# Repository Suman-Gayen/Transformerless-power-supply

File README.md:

# 🔌 Transformerless Power Supply PCB Design

A compact **Transformerless Power Supply Circuit** designed using **KiCad EDA 9.0.2** that converts AC mains voltage into regulated **5V DC output** without using a transformer.

---

## 📌 Project Overview

This project demonstrates the design of a low-cost transformerless power supply using:

- Capacitive voltage dropping
- Bridge rectification
- Filtering capacitors
- Zener protection
- LM7805 voltage regulation

The circuit is designed for low-power electronic applications where compact size and low component cost are important.

---

## 🖼 Project Schematic

```md

```

---

## ⚙ Features 

- AC to DC conversion
- 5V regulated DC output
- Compact PCB design
- Low component count
- LED power indication
- Overvoltage protection using Zener diode

---

## 🛠 Software Used

| Tool | Version |
|------|---------|
| KiCad EDA | 9.0.2 |

---

## 🔩 Components Used

| Component | Value / Part |
|-----------|--------------|
| U1 | LM7805 Voltage Regulator |
| D1–D4 | 1N4007 Rectifier Diodes |
| D5–D6 | Zener Diodes |
| D7 | LED |
| C1 | 0.1µF Capacitor |
| C2 | 100µF Capacitor |
| C3 | 2.2µF Capacitor |
| C4 | 470µF Capacitor |
| R1 | 1MΩ Resistor |
| R2, R3 | 20KΩ Resistors |
| R4 | 2.2KΩ Resistor |

---

## 🔍 Working Principle

### 1. Capacitive Voltage Dropping
The AC mains voltage is reduced using a non-polarized capacitor instead of a bulky transformer.

### 2. Rectification
Diodes D1–D4 form a bridge rectifier that converts AC voltage into pulsating DC.

### 3. Filtering
Capacitors smooth the rectified DC signal and reduce ripple voltage.

### 4. Voltage Regulation
The LM7805 regulator provides stable 5V DC output.

### 5. Protection
Zener diodes help protect the circuit from voltage spikes and overvoltage conditions.

---

## 📐 PCB Design Highlights

- Designed in KiCad EDA
- Compact component placement
- Easy routing structure
- Beginner-friendly PCB layout
- Suitable for low-power embedded applications

---

## ⚠ Safety Warning

> This project directly interfaces with AC mains voltage.

### Important Safety Notes:
- Do NOT touch the circuit while powered.
- Use proper insulation.
- Test carefully using safety precautions.
- Recommended for educational purposes only.
- Isolation transformer is recommended during testing.

---

## 🎯 Learning Outcomes

Through this project, I learned:

- Transformerless power supply design
- AC to DC rectification
- Voltage regulation using LM7805
- PCB schematic creation in KiCad
- Power electronics fundamentals
- Importance of electrical safety

---

## 🚀 Future Improvements

- Add fuse protection
- Add MOV surge protection
- Improve PCB isolation spacing
- Add output filtering enhancements
- Design compact single-layer PCB

---

## 📂 Project Structure

```bash
Transformerless-Power-Supply/
│
├── Schematic/
├── PCB_Layout/
├── Gerber_Files/
├── Images/
├── BOM/
└── README.md
```

---

## 🧠 Skills Demonstrated

- PCB Design
- Power Electronics
- KiCad EDA
- Circuit Design
- Hardware Development
- Electronic Prototyping

---

## 👨‍💻 Author

**Suman**  
Electronics & PCB Design Enthusiast

---

## 📜 License

This project is open-source and available for learning and educational purposes.

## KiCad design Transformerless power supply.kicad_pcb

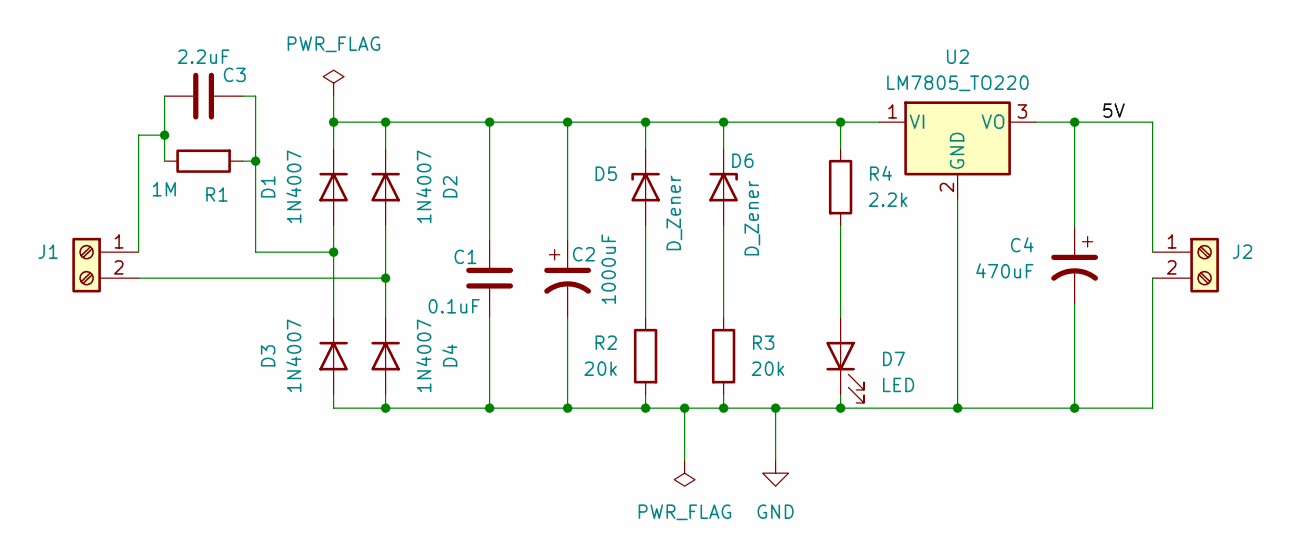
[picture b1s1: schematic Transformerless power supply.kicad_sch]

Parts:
C1: 0.1uF; C_Disc_D3.0mm_W1.6mm_P2.50mm
C2: 1000uF; CP_Radial_D10.0mm_P5.00mm
C3: 2.2uF; C_Rect_L18.0mm_W6.0mm_P15.00mm_FKS3_FKP3
C4: 470uF; CP_Radial_D10.0mm_P3.80mm
D1, D2, D3, D4: 1N4007; D_DO-41_SOD81_P10.16mm_Horizontal
D5, D6: D_Zener; D_A-405_P7.62mm_Horizontal
D7: LED; LED_D5.0mm
J1, J2: Screw_Terminal_01x02; TerminalBlock_bornier-2_P5.08mm
R1: 1M; R_Axial_DIN0207_L6.3mm_D2.5mm_P7.62mm_Horizontal
R2, R3: 20k; R_Axial_DIN0207_L6.3mm_D2.5mm_P7.62mm_Horizontal
R4: 2.2k; R_Axial_DIN0207_L6.3mm_D2.5mm_P7.62mm_Horizontal
U2: LM7805_TO220; TO-220-3_Vertical

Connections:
/5V: C4.1, J2.1, U2.3 (VO)
GND: C1.2, C2.2, C4.2, D3.2 (A), D4.2 (A), D7.1 (K), J2.2, R2.2, R3.2, U2.2 (GND)
unnamed: C3.2, D1.2 (A), D3.1 (K), R1.2
unnamed: C1.1, C2.1, D1.1 (K), D2.1 (K), D5.1 (K), D6.1 (K), R4.1, U2.1 (VI)
unnamed: D2.2 (A), D4.1 (K), J1.2
unnamed: D5.2 (A), R2.1
unnamed: D6.2 (A), R3.1
unnamed: D7.2 (A), R4.2
unnamed: C3.1, J1.1, R1.1

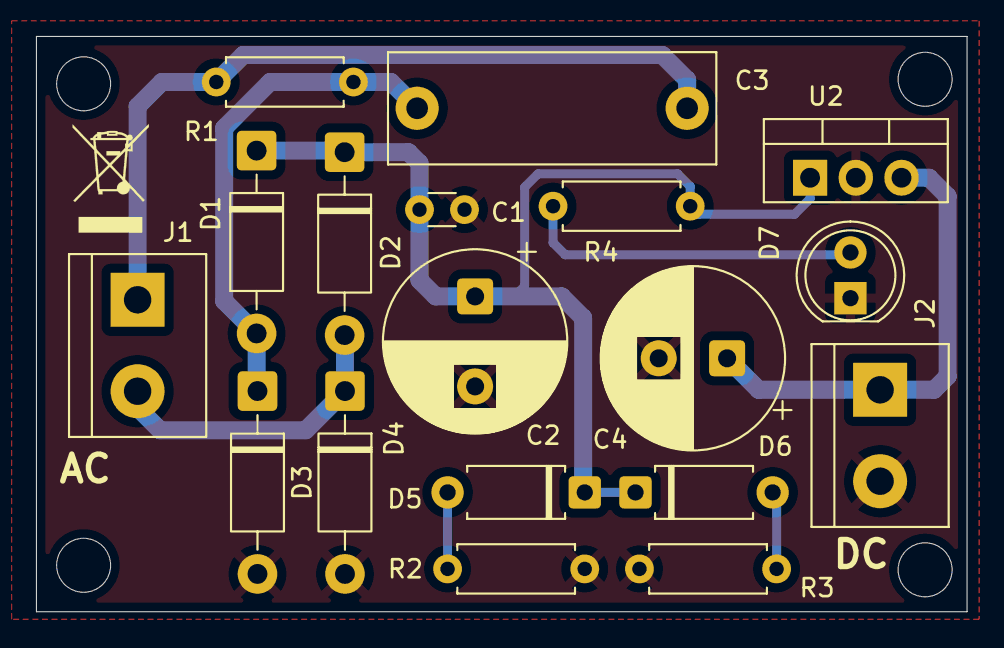
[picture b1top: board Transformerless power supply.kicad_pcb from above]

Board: 2 copper layers, 51.7 x 32.0 mm, 18 parts (0 on the bottom side), 9 nets.

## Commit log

2026-05-17 Revise README for Transformerless Power Supply project
    Updated README to provide detailed project information, including features, components, working principles, safety warnings, and future improvements.
2026-05-17 rename
2026-05-17 Remove placeholder for schematic image in README
    Remove placeholder text for schematic image.
2026-05-17 Fix formatting of Features section in README
2026-05-17 Remove recommended images section from README
    Removed section on recommended images for the repository.
